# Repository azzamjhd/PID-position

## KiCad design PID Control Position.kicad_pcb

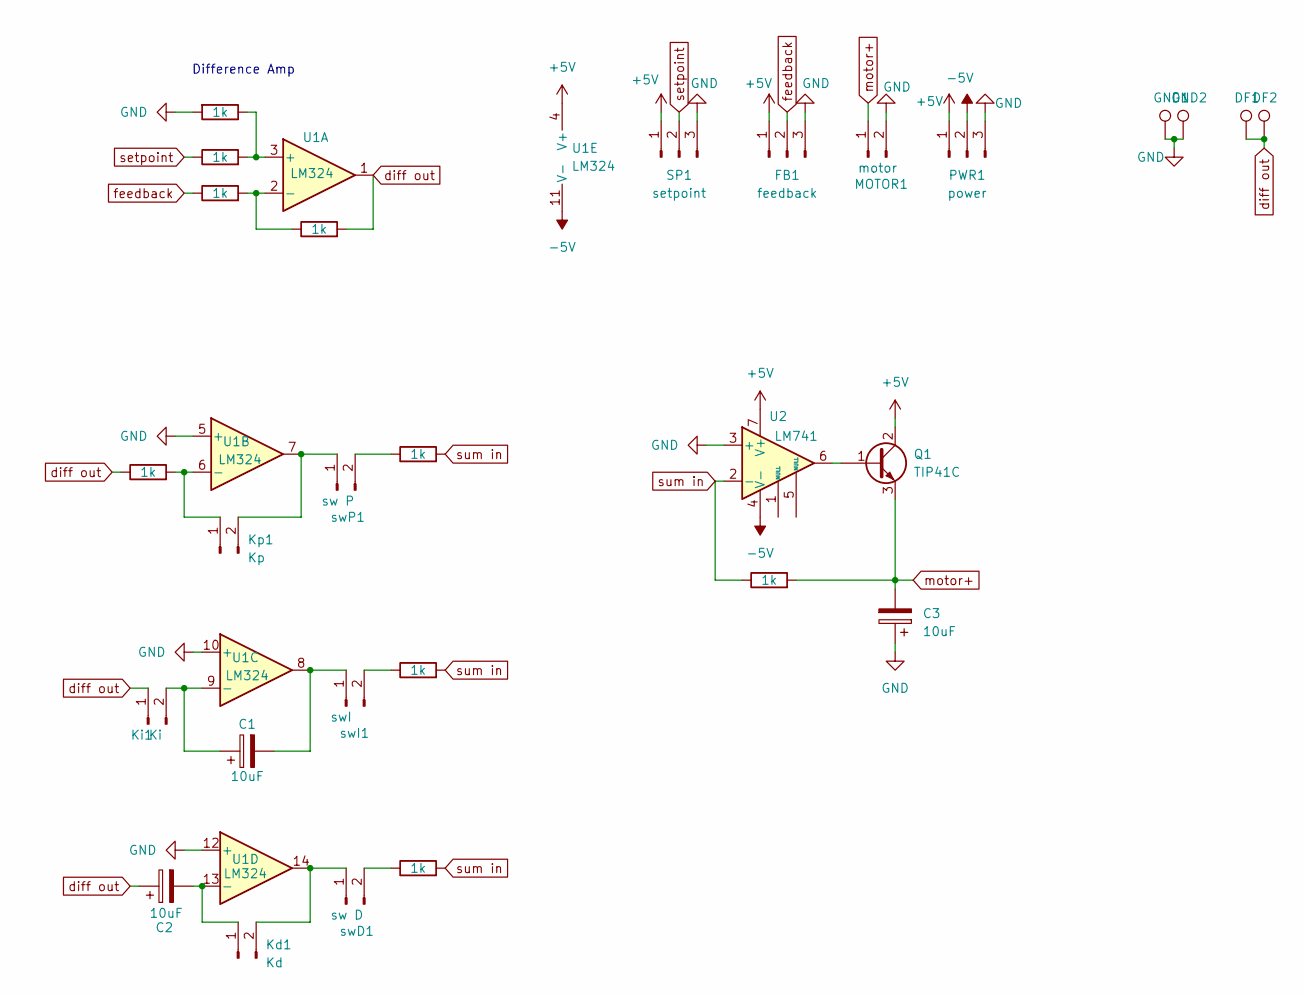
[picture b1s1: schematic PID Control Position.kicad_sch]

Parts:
C1, C2, C3: 10uF; CP_Radial_D5.0mm_P2.50mm
DF1, DF2: diffout; TestPoint_THTPad_2.0x2.0mm_Drill1.0mm
FB1: feedback; PinHeader_1x03_P2.54mm_Vertical
GND1, GND2: GND; TestPoint_THTPad_2.0x2.0mm_Drill1.0mm
Kd1: Kd; PinHeader_1x02_P2.54mm_Vertical
Ki1: Ki; PinHeader_1x02_P2.54mm_Vertical
Kp1: Kp; PinHeader_1x02_P2.54mm_Vertical
MOTOR1: motor; PinHeader_1x02_P2.54mm_Vertical
PWR1: power; PinHeader_1x03_P2.54mm_Vertical
Q1: TIP41C; TO-220-3_Vertical
R1, R2, R3, R4, R5, R6, R7, R8, R9: 1k; R_Axial_DIN0207_L6.3mm_D2.5mm_P10.16mm_Horizontal
SP1: setpoint; PinHeader_1x03_P2.54mm_Vertical
U1: LM324; DIP-14_W7.62mm_Socket
U2: LM741; DIP-8_W7.62mm_Socket
swD1: sw D; PinHeader_1x02_P2.54mm_Vertical
swI1: swI; PinHeader_1x02_P2.54mm_Vertical
swP1: sw P; PinHeader_1x02_P2.54mm_Vertical

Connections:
+5V: FB1.1, PWR1.1, Q1.2 (C), SP1.1, U1.4 (V+), U2.7 (V+)
-5V: PWR1.2, U1.11 (V-), U2.4 (V-)
GND: C3.1, FB1.3, GND1.1, GND2.1, MOTOR1.2, PWR1.3, R3.2, SP1.3, U1.5 (+), U1.10 (+), U1.12 (+), U2.3 (+)
unnamed: C2.2, Kd1.1, U1.13 (-)
unnamed: Kd1.2, U1.14, swD1.1
unnamed: C1.1, Ki1.2, U1.9 (-)
unnamed: Kp1.1, R5.2, U1.6 (-)
unnamed: Kp1.2, U1.7, swP1.1
unnamed: Q1.1 (B), U2.6
unnamed: R2.2, R3.1, U1.3 (+)
unnamed: R1.2, R4.1, U1.2 (-)
unnamed: R9.1, swD1.2
unnamed: C1.2, U1.8, swI1.1
unnamed: R8.1, swI1.2
unnamed: R7.1, swP1.2
diff out: C2.1, DF1.1, DF2.1, Ki1.1, R4.2, R5.1, U1.1
feedback: FB1.2, R1.1
motor+: C3.2, MOTOR1.1, Q1.3 (E), R6.2
setpoint: R2.1, SP1.2
sum in: R6.1, R7.2, R8.2, R9.2, U2.2 (-)

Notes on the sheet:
Difference Amp

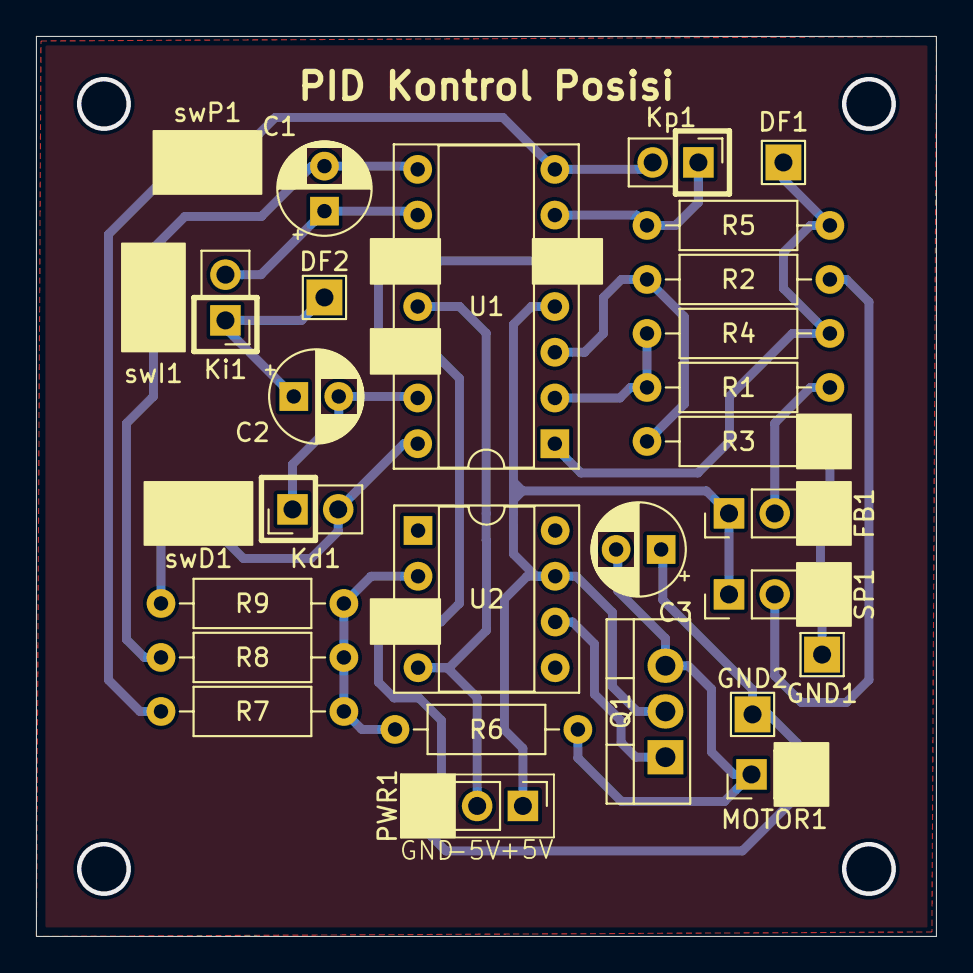
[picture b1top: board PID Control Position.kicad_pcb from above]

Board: 2 copper layers, 50.0 x 50.0 mm, 29 parts (0 on the bottom side), 20 nets.

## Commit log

2024-06-13 added pdf files
